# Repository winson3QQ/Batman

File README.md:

# Batman — Wi-Fi HaLow mesh on Raspberry Pi 4

Field notes from getting a **Morse Micro MM6108** Wi-Fi HaLow (802.11ah) radio working
over **SPI** on a Raspberry Pi 4, and building it into a batman-adv mesh node.

Hardware: Raspberry Pi 4 Model B + **Seeed WM1302 Pi HAT** + **Seeed Wio-WM6108**
mPCIe card (Quectel FGH100M-H / Morse Micro MM6108A1).

---

## TL;DR — the finding

The Morse Micro `morse_spi` driver fails to probe on a **stock** Raspberry Pi OS kernel:

```
morse_spi spi0.0: failed to init SPI with CMD63 (ret:-71)
```

The driver's SPI init sequence must send 144 training clocks with **chip-select
deasserted**. It does that by temporarily setting `SPI_CS_HIGH` to invert CS polarity.

On kernels **≥ 6.1** with **GPIO-descriptor chip-selects** (`cs-gpios`, which the
Pi 4 base device tree always uses), the SPI core sets `SPI_CS_HIGH` *itself* and
handles polarity through the GPIO descriptor flags. The driver's `|= SPI_CS_HIGH`
therefore becomes a **no-op**, and the training clocks go out with CS **asserted**.
The chip counts them as real bus traffic and its bit counter ends up exactly
**2 bits out of phase** for the rest of the session.

**Fix:** use `SPI_NO_CS` instead, so the core skips CS toggling entirely and the pin
stays high during training. → [`patches/0001-spi-use-SPI_NO_CS-for-training-sequence.patch`](patches/0001-spi-use-SPI_NO_CS-for-training-sequence.patch)

This is only needed because stock Raspberry Pi OS does **not** carry Morse Micro's
kernel patch (the one that defines `SPI_CONTROLLER_ENABLE_CS_GPIOD`). Their own
OpenWrt / `MorseMicro/rpi-linux` builds do.

Three things were required, all necessary:

1. Driver from the **MM6108 product line** — tag `mm6108-2.0.1`, *not* `mm8108-*`
2. The **`SPI_NO_CS` patch** above
3. Module parameters `enable_ext_xtal_init=1 bcf=bcf_fgh100mhaamd.bin`

Result:

```
morse_spi spi0.0: Loaded firmware from morse/mm6108.bin, size 468304, crc32 0xbe7b5c8f
morse_spi spi0.0: Loaded BCF from morse/bcf_fgh100mhaamd.bin, size 1251, crc32 0x941b2a82
```

---

## Then: the shortcut we should have found first

After all of the above, the driver worked — but a HaLow *link* still could not be
established, because Debian's stock `wpa_supplicant` (v2.10) contains **zero** S1G /
802.11ah support, and `hostapd` / `morse_cli` were not present at all.

It turns out **[OpenMANET](https://openmanet.github.io/docs/)** publishes a prebuilt
OpenWrt image for *exactly* this hardware combination — it lists
"Seeed WM1302 + Wio-WM6108" as a supported SPI setup, and the image ships
`wpa_supplicant_s1g`, `hostapd_s1g`, `morse-bcf-info` and `batctl` alongside the driver,
with 802.11s + BATMAN-V already wired up.

Its `mm610x-spi.dtbo` uses the **identical GPIO mapping** we had arrived at by hand.

**Lesson:** search for prebuilt firmware before rebuilding a vendor driver. The
`SPI_NO_CS` finding still stands for anyone running the Morse driver on a stock,
unpatched kernel — but if you just want a working mesh node, flash OpenMANET.

See [`docs/openmanet.md`](docs/openmanet.md).

---

## Contents

| Path | What |
|---|---|
| [`docs/hardware.md`](docs/hardware.md) | Hardware stack, GPIO map, device tree |
| [`docs/root-cause.md`](docs/root-cause.md) | Symptom → diagnosis → root cause, in full |
| [`docs/building-the-driver.md`](docs/building-the-driver.md) | Build instructions and the gotchas |
| [`docs/openmanet.md`](docs/openmanet.md) | The OpenMANET route |
| [`docs/flashing-and-recovery.md`](docs/flashing-and-recovery.md) | **Why `dd`-flashing an OpenWrt image leaves the old config intact**, and how to tell |
| [`docs/led-indicator.md`](docs/led-indicator.md) | Two-LED field status indicator — what each pattern means and why |
| [`docs/cloning-a-node.md`](docs/cloning-a-node.md) | **Building the second node by copying the first**, and the seven values that must not be copied |
| [`docs/pi5-rp1-bringup.md`](docs/pi5-rp1-bringup.md) | **Pi 5 / Pi 500 (RP1) only** — the two RP1-specific root causes and the Pi 5 overlays |
| [`patches/`](patches/) | The `SPI_NO_CS` patch |
| [`scripts/`](scripts/) | `flash-card.sh` (write + actually clear a card), `meshled` (LED daemon), `meshtest` (mesh health report), the uci cloning tools |
| [`tools/`](tools/) | Python SPI diagnostic scripts (via `spidev`) |

## Also worth reading

If you flash OpenWrt to SD cards with `dd`, [`docs/flashing-and-recovery.md`](docs/flashing-and-recovery.md)
is the most generally useful thing here. The image covers only the boot partition and
the squashfs — the `rootfs_data` overlay after it is never written, so the device boots
with its entire previous configuration restored while every verification you would
normally run comes back green.

## Status

- ✅ Driver probes, firmware + BCF load, netdev appears
- ✅ Root cause understood and patched
- ✅ OpenMANET 1.7.0 `rpi4-mm6108-spi` flashed, overlay wiped, **booted and verified**
- ✅ HaLow radio up under OpenMANET: `RPI RPI4-MM6108 (SPI)`, `wlan0`, 923 MHz @ 2 MHz BW, 27 dBm
- ✅ Node 1 configured: 802.11s mesh + SAE, BATMAN_V, hostname `manet01`, 2.4 GHz off
- ✅ Two-LED field status indicator installed and verified — [`docs/led-indicator.md`](docs/led-indicator.md)
- ✅ Node 2 built by **cloning node 1's uci config**, no wizard — [`docs/cloning-a-node.md`](docs/cloning-a-node.md)
- ✅ Second MM6108 set probes and loads firmware, radio up at 923 MHz / 2 MHz
- ⏳ Two nodes not yet powered simultaneously, so the mesh has not been formed
- ⏳ TX still not proven to radiate — the first `batctl n` neighbour will settle it
- ⏳ `meshtest` written but not yet run against a real peer

## License

Repository content is MIT (see [`LICENSE`](LICENSE)), except where noted:
- The patch in `patches/` applies to Morse Micro's driver, which is GPL-2.0-or-later;
  the patch is offered under the same terms as the code it modifies.
- `deploy/ots/patches/` contains a modified OpenTAKServer source file and its patch/generator,
  which are GPL-3.0-or-later like OpenTAKServer itself (see that directory's README).

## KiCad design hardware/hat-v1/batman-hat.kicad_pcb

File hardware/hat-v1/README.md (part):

# Batman HAT v1：電路圖（M2）

設計規格見 [`docs/design/hat-v1-spec.md`](../../docs/design/hat-v1-spec.md)。本資料夾是依規格產生的 **KiCad 7 電路圖**，狀態：**草稿，尚未送板廠**。

## 看圖

- **PDF**：[`out/batman-hat-schematic.pdf`](out/batman-hat-schematic.pdf)，共 10 頁：總覽 1 頁，加上 9 個功能區塊各 1 頁。
- **自動檢查報告**：[`out/check-report.md`](out/check-report.md)
- **材料清單草稿**：[`out/bom-draft.csv`](out/bom-draft.csv)。LCSC 料號在 M3 階段補齊。
- **用 KiCad 開**：開 `batman-hat.kicad_pro`。

### 這份電路圖怎麼讀

- 採用「**標籤式**」畫法：元件之間不拉長線，每支腳旁邊標一個**網路名稱**，**名稱相同就代表接在一起**。
  - 方框形的標籤是跨頁共用的網路。
  - 純文字的標籤只在該頁內使用。
- 腳上打 **×** 的，是刻意不接。
- 被紅色 **×** 劃掉的元件是**預留不焊**（DNP），用來日後微調。
- 每頁左下角的 **NOTES** 寫了每個元件為什麼這樣接、數值怎麼來的。

| 頁 | 檔案 | 內容 |
|---|---|---|
| 2 | `power_in` | 電池焊墊、突波保護、eFuse 與反接保護、整台電流量測（INA226 #1）、電池偵測 |
| 3 | `power_5v` | 5 V 降壓（給 Pi）、理想二極體（防止 Pi 的 USB-C 倒灌）、綠燈 |
| 4 | `power_3v3` | 電源二選一（電池 / Pi 5 V）、3.3 V 降壓（給 HaLow）、HaLow 電流量測（INA226 #2）、濾波 |
| 5 | `softpower` | LTC2955 軟開關機、AUTO-ON 跳線、電源鍵 |
| 6 | `pi_header` | 40-pin 排母、固定孔（2026-09-28 拿掉 ID EEPROM，改用 `config.txt`） |
| 7 | `halow` | mPCIe 插座（Wio-WM6108）、大電容 |
| 8 | `security` | TPM 2.0 SLB9672、ATECC608C、RTC RV-3028 與超級電容 |
| 9 | `gnss` | MAX-M10S 定位模組、主動式天線供電、U.FL |
| 10 | `debug` | Tag-Connect 除錯焊墊、所有測試點（值欄寫了正常讀值）、電源旗標 |

## 怎麼產生（不要直接改 `.kicad_sch`）

**唯一的資料來源是 `gen/design.py`**：所有元件、數值、接線都寫在這裡。改完後執行：

```sh
./build.sh      # 需要 KiCad 7（kicad-cli）與 python3
```

依序產生：

1. 電路圖
2. 檢查報告
3. 材料清單
4. PDF

檢查沒過就停下來，並印出錯誤。

| 檔案 | 作用 |
|---|---|
| `gen/design.py` | 設計資料：元件、數值、接線，以及檢查程式要用的規格事實（GPIO 表、電壓上限） |
| `gen/symbols.py` | 元件符號與接腳對照 |
| `gen/gen_sch.py` | 產生 KiCad 7 電路圖 |
| `gen/check.py` | 檢查（見下） |
| `gen/bom.py` | 材料清單草稿 |

## 自動檢查做了什麼

`gen/check.py` 會做以下檢查：

1. **接線比對**：請 KiCad 自己匯出接線表（netlist），和 `design.py` **逐腳比對**，目前 557 支腳全部一致。產生程式若有錯，例如標籤沒對到腳、兩個網路被接在一起，這一步會抓到。
2. **GPIO 表**：Pi 排針的 28 支 GPIO 和規格 §4.2 逐一比對。
3. **I2C 位址**不重複：0x36 / 0x40 / 0x41 / 0x52。
4. **TPM 與 SPI1 網路上沒有任何測試點**（規格 §5.1 的資安要求）。
5. **電壓上限**：
   - 對有耐壓限制的接腳（例如 TPS62933F 的 EN 最高 6 V、LTC2955 的 KILL 最高 6 V），用該網路最壞情況的電壓比對規格書的絕對最大值。
   - 接到 Pi GPIO 的網路都不可超過 3.3 V。
6. **只接到一支腳的網路**：這類網路列為錯誤，除非在 `SINGLE_PIN_OK` 寫明理由（例如只接測試點的除錯腳）。
7. **設定點**：從電阻值反算以下各項，和規格比對：
   - eFuse 的欠壓 / 過壓 / 限流門檻
   - 5 V 與 3.3 V 的輸出電壓
   - 5 V 降壓的硬體欠壓門檻
   - AUTO-ON 門檻

KiCad 7 的命令列沒有 ERC（電氣規則檢查），上面這些自寫檢查就是替代。用 KiCad 圖形介面開啟時，仍可手動執行 ERC 做第二道檢查。

## 已知待辦（送板廠前必須完成）

| 項目 | 狀態 |
|---|---|
| `batman:` 開頭的自製封裝 | ✅ mPCIe 5.2H、RV-3028 已依原廠圖面畫好；TI 功率 FET、SLB9672 改用 KiCad 內建封裝；**CPH3225A、電池焊墊、卡片固定柱仍是佔位封裝** |
| LCSC 料號、JLC 基礎料 / 擴展料、庫存 | M3 |
| 電感、磁珠的實際型號與規格（Isat、DCR） | M3 查證 |
| MAX-M10S 的 VIO_SEL、V_BCKP 接法 | ✅ 已依規格書 R08 確認：VIO_SEL 空接 = 3.3 V、V_BCKP 1.65–3.6 V 接 3.3 V |
| GNSS 主動式天線供電與短路偵測 | ✅ 依整合手冊 R05 圖 38 的**三腳天線監控**：P-FET 開關（LNA_EN 控制）、10 Ω 感測電阻、OPA333 比較器 → 偵測短路 / 斷線並自動切斷、恢復天線供電；天線由 3V3_GNSS 供電（不再受 VCC_RF 50 mA 限制）。GNSS 的 I2C 腳改作監控用（CFG-I2C-ENABLED=0） |
| RV-3028 的 EVI 閒置處理 | ✅ Application Manual §7.1：「EVI 不可空接，經電阻接 VSS」→ 維持 100 kΩ 到地；另依 §7.3 在 VBACKUP 加 100 nF（C77） |
| 卡片固定柱高度 | 第一批板子量測（規格 V14） |

## 對抗式審查修正紀錄（電路圖 v0.1，2026-09-27）

兩位獨立審查者。

- **電源審查**：沒有阻斷級問題，3 個重大、7 個次要。
- **數位 / 資安 / 製造審查**：1 個阻斷級、4 個重大、6 個次要。
- 兩份審查都確認：接腳、I2C 位址、GPIO 對應都沒有接錯。

以下是修正項目：

| 嚴重度 | 問題 | 修正 |
|---|---|---|
| 重大 | AUTO-ON 門檻（6.25 V）可能低於 5 V 降壓的開機門檻：電池慢慢回升時，LTC2955 先開、Pi 還沒電 → 0.5 秒後又關掉，而且之後不會再自動開機 | R31 改 787 kΩ → AUTO-ON 7.10 V（最低 6.74 V，高於降壓的最高門檻 6.55 V）；檢查程式加入最壞情況比對 |
| 重大 | BENCH 跳線焊上後，R23 拖低 LTC_ENB，LTC2955 關不掉 5 V → 電池供電時無法斷電 | R23 改 4.7 MΩ（2026-09-28 方案 D 後 BENCH 已取消，R23 改當 EN 上拉） |
| 重大 | 過壓切斷點（18.0–18.7 V）離 4S 滿電 16.8 V 太近；插電池的振鈴會觸發過壓，且可能一直關著不恢復 | R3 改 1.50 MΩ → 19.2 V 切斷、最低 17.44 V 恢復；電池輸入加 1 Ω + 10 µF 阻尼 |
| 重大 | A 級元件在 KiCad 沒標不焊，匯出給 JLC 會被一起焊上 | A 級元件自動標為 DNP（電路圖上會被劃掉，這是刻意的：由台灣補焊） |
| 重大 | 天線線短路 → 0402 電阻燒掉、拖垮 Pi 3.3 V | R81 改 47 Ω 1206（短路約 70 mA、0.23 W，在額定內）；待整合手冊再確認 |
| 重大 | 量產板的 Tag-Connect 仍接著 HaLow SPI（金鑰會經過）與 root 序列埠 | 每條線串 0 Ω（R40–R47）：開發板焊、量產板不焊；VCC 腳串 1 kΩ（R48） |
| 重大 | 材料清單無法直接下單 | 只有銅箔的項目（測試焊墊、跳線、固定孔、Tag-Connect）移出材料清單；LCSC 料號在 M3 補齊 |
| 阻斷 | 自製封裝不存在 | 可用現成的先換：電感 `L_Coilcraft_XxL4030`、TI 功率電晶體 `VSON-8 NexFET`（汲極合併為第 5 腳）、TPM `QFN-32 5×5 散熱墊 3.6 mm`。其餘（mPCIe、RTC、超級電容、電池焊墊、固定柱）在 M4 建立 |
| 次要 | 電容耐壓與直流偏壓降容；eFuse IN 腳缺電容；TPS62933F EN 只有 0.7 µA 上拉、容易受干擾；5 V 最壞可到 5.33 V | 輸入電容改 10 µF 50 V X7R 1210；VCAP 改 220 nF 25 V；加 C9 100 nF、C32 2.2 nF；R13/R14 改 0.5%（最壞 5.29 V） |
| 次要 | 待機耗電約 2 mA（主要是 eFuse 本身） | 電池偵測分壓改 1 MΩ；其餘寫進文件（3 Ah 約 60 天放完） |
| 次要 | GPIO14/15 在 Pi 4 預設是 mini-UART，不是 UART0 | 網路改名 `CONSOLE_TX/RX` |
| 次要 | LED 規格要 0402 | 改 0402 |
| 次要 | 隔離跳線切斷後，晶片仍會經 I2C / SPI / UART 被反向供電 | 寫進元件備註 |
| 次要 | I2C 400 kHz 時 ATECC608 喚醒脈衝不夠長 | 軟體維持 100 kHz（寫進規格 §7） |
| 次要 | 沒有光學定位點 | M4 畫電路板時加 3 個 |

**已知、接受的行為**（寫給使用者）：
- 用 USB-C 開發時才插上電池（且沒焊 AUTO-ON），LTC2955 會以「關機」狀態啟動，把 HaLow 的 3.3 V 關掉 → 先插電池再插 USB-C，或按一下電源鍵。
- LTC2955 開機遮蔽期間（最多 0.72 秒），HaLow 卡可能經 SPI 腳微量反向供電給 Pi。

## 第一版擺位（M4 第 1 步，尚未走線）

- **產生方式**：`python3 gen/gen_fp.py && python3 gen/gen_pcb.py`，會產生 `batman-hat.kicad_pcb`、[`out/floorplan.png`](out/floorplan.png) 與 [`out/floorplan-report.md`](out/floorplan-report.md)。
- **固定位置的零件**依機構尺寸擺放：
  - HAT 外框 65 × 56.5 mm
  - 40-pin 排母（在背面）
  - 4 個固定孔
  - mPCIe 插座與卡片外框：卡片平躺在板子上方，插座在右側
- **其他零件**依功能分區自動排，**卡片正下方只放 ≤ 1.9 mm 高**、不發熱、不需要摸得到的零件。
- **自製封裝**：`batman.pretty` 裡的 mPCIe 插座是照連欣規格書畫的；RTC 依 Application Manual §8.1 畫好；超級電容、電池焊墊、固定柱是**佔位封裝**（標 PLACEHOLDER），送板廠前要依原廠焊墊圖重畫。
- **Pi 4 Wi-Fi 天線禁佈區**的位置是推論，要對照 Pi 4 機構圖確認。

### 測試點（使用者決定，2026-09-27）

| 類型 | 位置 | 內容 |
|---|---|---|
| 可夾的大焊墊（Keystone 5015） | 正面 | 電池 VBAT、5V、HaLow 3.3V、GND |
| 小探針焊墊（1–1.5 mm） | **背面（接 Pi 那面）** | 其他電源軌、eFuse / 降壓 / 軟開關機的控制訊號、GNSS 重置、RTC 輸出、分流電阻的 Kelvin 點 |
| 不另設測試點 | 40-pin 排母的焊點（穿到正面露出） | I2C、UART5、PPS、INT/KILL、BAT_PRESENT、ALERT、HaLow reset/wake（清單在 `design.py` 的 `HEADER_PROBE`，檢查程式會確認都在排針上） |

- **怎麼量背面的焊墊**：焊墊都排在板子左、右、下三邊、離板邊約 3 mm 內。用 40-pin 延長排針（stacking header）把 HAT 墊高，探針就能從側面點到；要長時間觀察（示波器看時序）就焊一條 30 AWG 細線拉出來。
  - 左邊：eFuse / 軟開關機 / 5 V 控制訊號
  - 右邊：GNSS / RTC 相關
  - 下邊：其他電源軌
- **TPM / SPI1 仍然不設任何測試點。**

### 雜訊擺位原則（2026-09-27）

- **兩顆降壓的開關核心放在板子下緣**，也就是晶片、電感、輸入電容這幾顆：
  - 遠離右上角的 GNSS，距離約 35 mm。
  - 遠離左邊 HaLow 卡的天線端。
- **這兩組的直流側零件放在卡片下方、最靠近下緣的一條**：輸出電容、理想二極體。
- **上方長條只放安靜的零件**：GNSS、Tag-Connect、可夾測試點、eFuse。eFuse 不會切換開關，所以不產生開關雜訊。
- **實際效果仍需上機量測**，見規格 V7 / V11：降壓滿載時 GNSS 的 C/N0（載波雜訊比，衡量衛星訊號強度），以及 HaLow 接收靈敏度。

## 送板廠前的模擬（`python3 sim/run_all.py` → [`out/sim/sim-report.md`](out/sim/sim-report.md)）

| 項目 | 工具 | 結果 |
|---|---|---|
| S1 插電池瞬間的振盪 | ngspice（KiCad 內建） | 原本 1 Ω + 10 µF 阻尼在 16.8 V 時會衝到 20.1 V → 改成 **0.47 Ω + 2 × 10 µF**。線長 ≤ 0.7 m 時峰值低於過壓門檻。1.5 m 長線仍會略超過，但持續 7.8 µs，短於 eFuse 最短反應時間 8.5 µs；就算觸發也只是延後開機，不會損壞 |
| S2 HaLow 3.3 V：π 濾波 + 發射突波 | ngspice | 1.2 A 突波下插座端最低 3.26 V（mPCIe 下限 3.0 V）；濾波共振 78 mΩ @ 13.8 kHz。**聚合物電容 C62 必要**：拿掉的話共振升到 250 mΩ |
| S3 開關機情境（8 種） | 依規格書寫的行為模型 | 全部符合設計意圖 |
| S4 電池慢慢回升（蒙地卡羅，400 次） | 行為模型 | 目前設計 **0 / 400** 卡在關機；審查前的 681 kΩ 有 274 / 400 卡住 → 證實審查的修正是必要的 |

- 所有假設（線長、電容降額、HaLow 發射電流等）都列在報告最後一節，有更準的數據時改數字重跑即可。
- 雜訊干擾 GNSS / HaLow 無法可靠模擬，仍需第一批板子實測（規格 V7 / V11）。

## LCSC 料號（M3 草稿，`gen/lcsc.py` → [`out/lcsc-report.md`](out/lcsc-report.md)、[`out/bom-jlc.csv`](out/bom-jlc.csv)）

這個環境連不到 JLC 和 LCSC 官網（網路政策擋住），所以用以下三個離線來源：

1. **jlcparts 完整資料庫**：GitHub 公開，2026-09-27 16:21 UTC 快照，101 萬筆。
   - 限制：目前只收 LCSC 編號 **C6374508 以後**的零件，所以舊編號的零件查不到，包括大部分基礎料和 TI 的 IC。
2. **JLC 基礎料 / 優選料編號清單**：CDFER/jlcpcb-parts-database 每日自動抓取，2026-09-27 更新，共 3,493 個編號。只有編號，沒有規格。
3. **常用基礎料對照**：例如 0402 10 kΩ = C25744。這是記憶中的對照，只有在該編號**確認列於基礎料清單**時才採用；「編號對應什麼規格」要在上傳 JLC 時核對。

| 狀態 | 行數 | 意思 | 你要做的 |
|---|---|---|---|
| DB | 23 | 快照裡查到，有庫存 | 下單前看一下庫存有沒有變 |
| BASIC-verify | 13 | JLC 基礎料（省擴展料費） | 上傳 BOM 後，核對 JLC 顯示的規格和報告「note」欄一致 |
| SEARCH | 32 | 快照裡沒有 | 到 jlcpcb.com/parts 用 MPN 搜尋，或讓 JLC 的 BOM 工具依 MPN 自動配對 |
| NOT-JLC | 40 | A 級元件（台灣補焊）或只有銅箔 | A 級向 DigiKey / Mouser 等原廠授權通路採購 |
| DNP | 2 | 不焊 | — |

- **中國廠商**：SURGING（SMBJ20CA）、hongjiacheng（BSS138）、FOJAN（3.9 kΩ）、Chinocera（47 µF）、連欣（mPCIe 插座），都是 C 級被動 / 分離元件，依規格 §5.8 可用。報告的「origin」欄標了每一家的總部所在地。
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
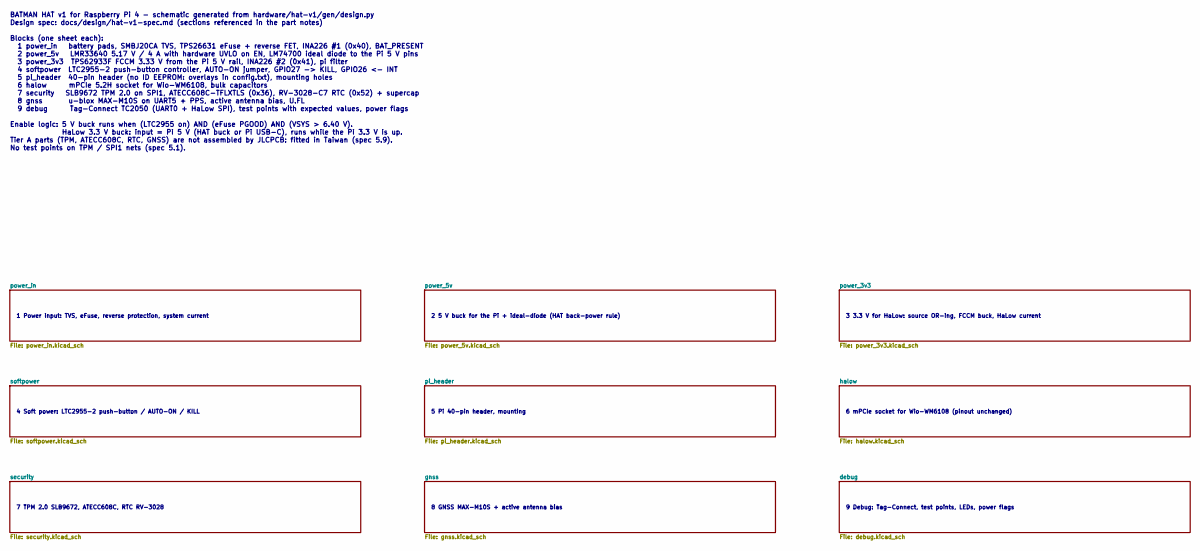
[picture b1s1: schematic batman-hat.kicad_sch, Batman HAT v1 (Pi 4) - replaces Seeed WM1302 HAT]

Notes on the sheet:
1 Power input: TVS, eFuse, reverse protection, system current
2 5 V buck for the Pi + ideal-diode (HAT back-power rule)
3 3.3 V for HaLow: source OR-ing, FCCM buck, HaLow current
4 Soft power: LTC2955-2 push-button / AUTO-ON / KILL
5 Pi 40-pin header, mounting
6 mPCIe socket for Wio-WM6108 (pinout unchanged)
7 TPM 2.0 SLB9672, ATECC608C, RTC RV-3028
8 GNSS MAX-M10S + active antenna bias
9 Debug: Tag-Connect, test points, LEDs, power flags
BATMAN HAT v1 for Raspberry Pi 4 - schematic generated from hardware/hat-v1/gen/design.py Design spec: docs/design/hat-v1-spec.md (sections referenced in the part notes) Blocks (one sheet each): 1 power_in battery pads, SMBJ20CA TVS, TPS26631 eFuse + reverse FET, INA226 #1 (0x40), BAT_PRESENT 2 pow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

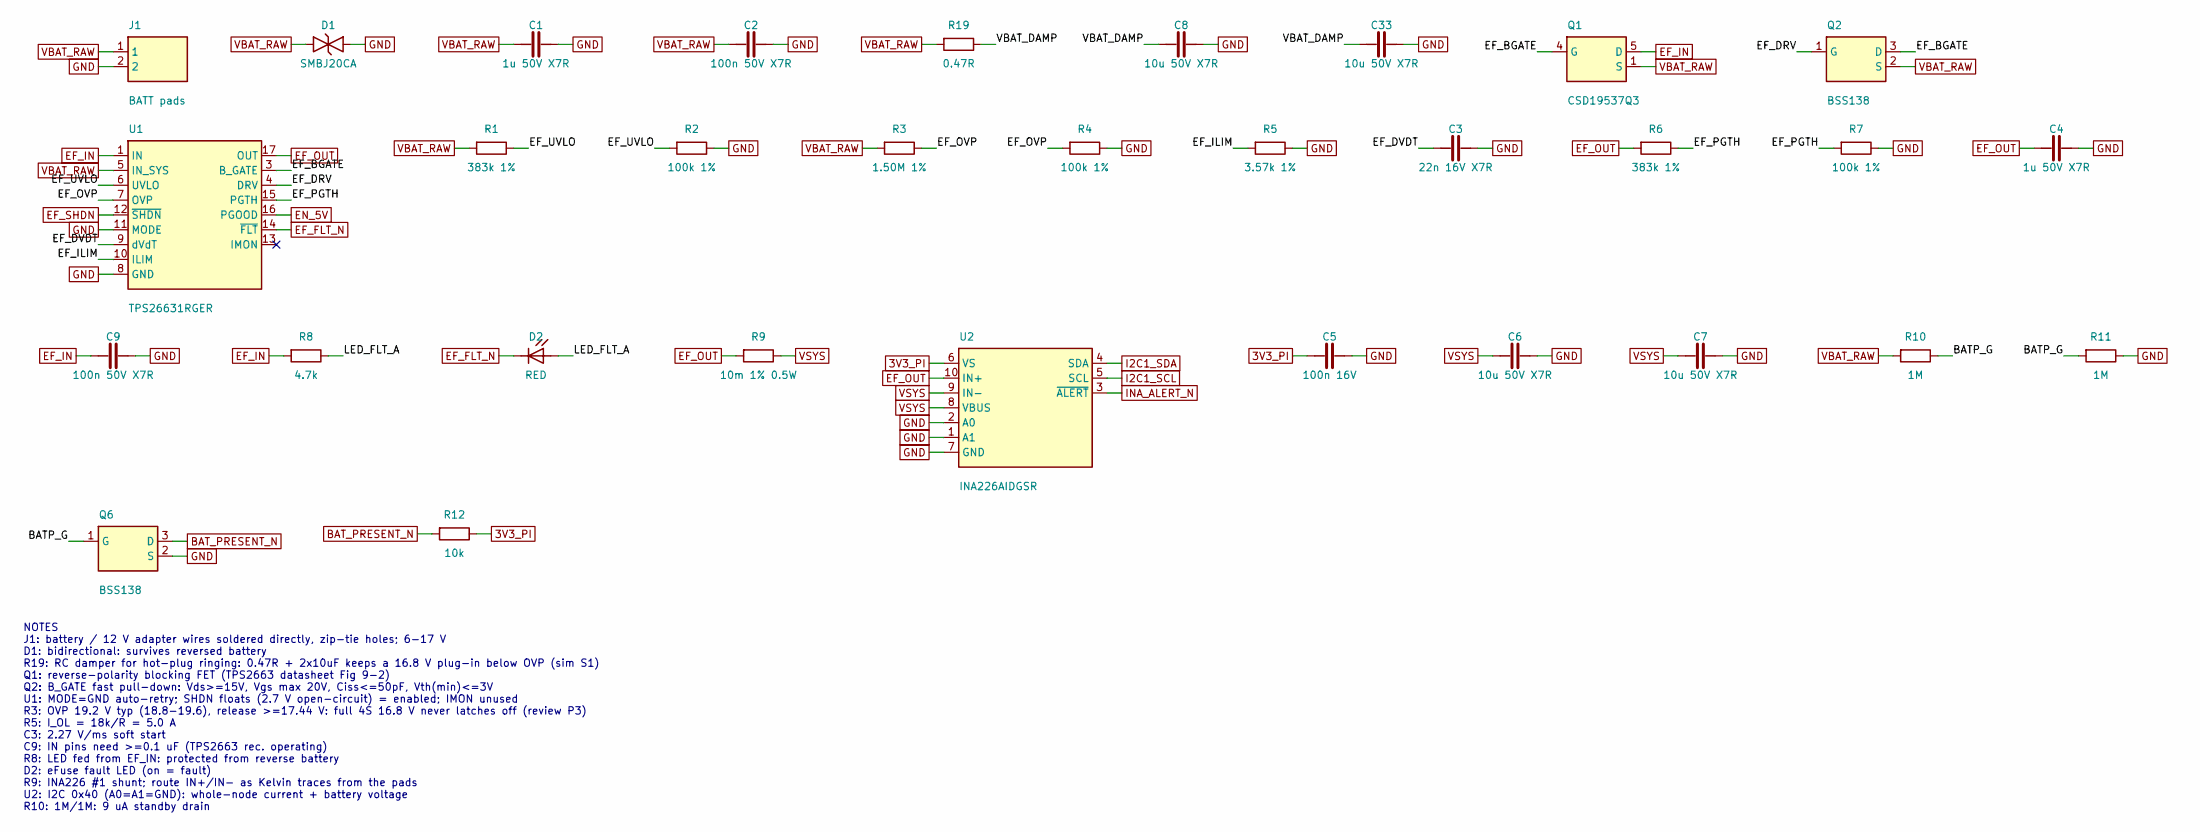
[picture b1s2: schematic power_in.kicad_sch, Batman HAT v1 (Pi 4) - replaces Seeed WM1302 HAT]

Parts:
C1, C4: 1u 50V X7R; C_0805_2012Metric
C2, C9: 100n 50V X7R; C_0402_1005Metric
C3: 22n 16V X7R; C_0402_1005Metric
C5: 100n 16V; C_0402_1005Metric
C6, C7, C8, C33: 10u 50V X7R; C_1210_3225Metric
D1: SMBJ20CA; D_SMB; MPN SMBJ20CA
D2: RED; LED_0402_1005Metric
J1: BATT pads; BattPads_2x_3x5mm_StrainRelief
Q1: CSD19537Q3; VSON-8_3.3x3.3mm_P0.65mm_NexFET; MPN CSD19537Q3
Q2, Q6: BSS138; SOT-23; MPN BSS138
R1, R6: 383k 1%; R_0402_1005Metric
R2, R4, R7: 100k 1%; R_0402_1005Metric
R3: 1.50M 1%; R_0402_1005Metric
R5: 3.57k 1%; R_0402_1005Metric
R8: 4.7k; R_0603_1608Metric
R9: 10m 1% 0.5W; R_1206_3216Metric
R10, R11: 1M; R_0402_1005Metric
R12: 10k; R_0402_1005Metric
R19: 0.47R; R_0805_2012Metric
U1: TPS26631RGER; Texas_RGE0024H_VQFN-24-1EP_4x4mm_P0.5mm_EP2.7x2.7mm_Thermal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; MPN TPS26631RGER
U2: INA226AIDGSR; VSSOP-10_3x3mm_P0.5mm; MPN INA226AIDGSR

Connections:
BATP_G: Q6.1 (G), R10.2, R11.1
BAT_PRESENT_N: Q6.3 (D), R12.1; also elsewhere on the board
EF_BGATE: Q1.4 (G), Q2.3 (D), U1.3 (B_GATE)
EF_DRV: Q2.1 (G), U1.4 (DRV)
EF_DVDT: C3.1, U1.9 (dVdT)
EF_FLT_N: D2.1, U1.14 (~FLT); also elsewhere on the board
EF_ILIM: R5.1, U1.10 (ILIM)
EF_IN: C9.1, Q1.5 (D), R8.1, U1.1 (IN), U1.2 (IN)
EF_OUT: C4.1, R6.1, R9.1, U1.17 (OUT), U1.18 (OUT), U2.10 (IN+); also elsewhere on the board
EF_OVP: R3.2, R4.1, U1.7 (OVP)
EF_PGTH: R6.2, R7.1, U1.15 (PGTH)
EF_SHDN: U1.12 (~SHDN); also elsewhere on the board
EF_UVLO: R1.2, R2.1, U1.6 (UVLO)
EN_5V: U1.16 (PGOOD); also elsewhere on the board
GND: C1.2, C2.2, C3.2, C4.2, C5.2, C6.2, C7.2, C8.2, C9.2, C33.2, D1.2, J1.2, Q6.2 (S), R2.2, R4.2, R5.2, R7.2, R11.2, U1.8 (GND), U1.11 (MODE), U1.25 (GND), U2.1 (A1), U2.2 (A0), U2.7 (GND); also elsewhere on the board
I2C1_SCL: U2.5 (SCL); also elsewhere on the board
I2C1_SDA: U2.4 (SDA); also elsewhere on the board
INA_ALERT_N: U2.3 (~ALERT); also elsewhere on the board
LED_FLT_A: D2.2, R8.2
VBAT_DAMP: C8.1, C33.1, R19.2
VBAT_RAW: C1.1, C2.1, D1.1, J1.1, Q1.1 (S), Q1.2 (S), Q1.3 (S), Q2.2 (S), R1.1, R3.1, R10.1, R19.1, U1.5 (IN_SYS); also elsewhere on the board
VSYS: C6.1, C7.1, R9.2, U2.8 (VBUS), U2.9 (IN-); also elsewhere on the board

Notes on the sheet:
NOTES J1: battery / 12 V adapter wires soldered directly, zip-tie holes; 6-17 V D1: bidirectional: survives reversed battery R19: RC damper for hot-plug ringing: 0.47R + 2x10uF keeps a 16.8 V plug-in below OVP (sim S1) Q1: reverse-polarity blocking FET (TPS2663 datasheet Fig 9-2) Q2: B_GATE fast pu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

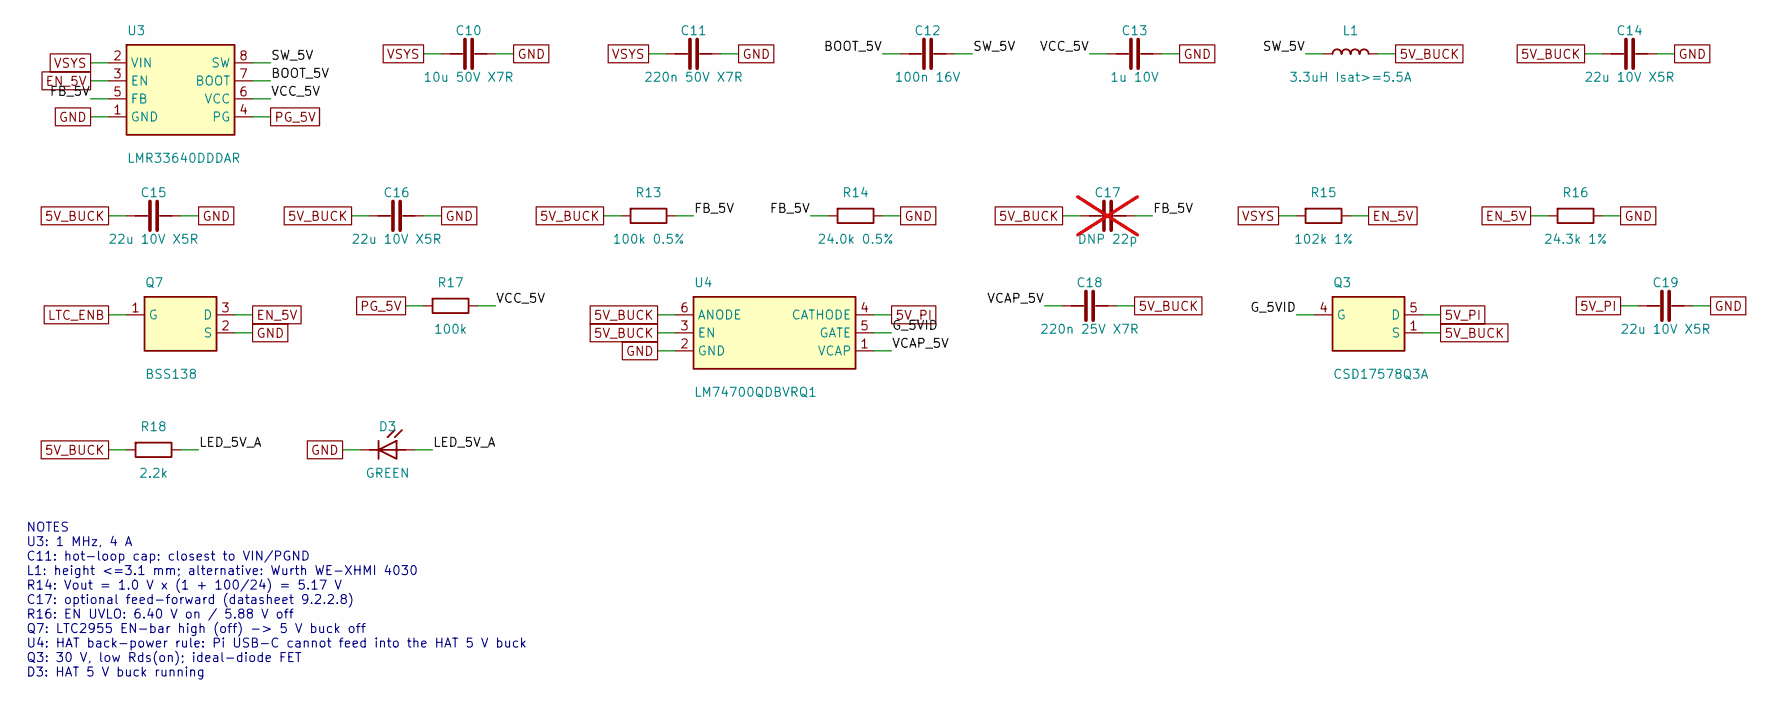
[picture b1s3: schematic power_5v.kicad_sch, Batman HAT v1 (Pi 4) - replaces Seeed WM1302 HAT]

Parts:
C10: 10u 50V X7R; C_1210_3225Metric
C11: 220n 50V X7R; C_0603_1608Metric
C12: 100n 16V; C_0402_1005Metric
C13: 1u 10V; C_0402_1005Metric
C14, C15, C16, C19: 22u 10V X5R; C_0805_2012Metric
C17: DNP 22p; C_0402_1005Metric; not fitted
C18: 220n 25V X7R; C_0603_1608Metric
D3: GREEN; LED_0402_1005Metric
L1: 3.3uH Isat>=5.5A; L_Coilcraft_XxL4030; MPN XGL4030-332MEC
Q3: CSD17578Q3A; VSON-8_3.3x3.3mm_P0.65mm_NexFET; MPN CSD17578Q3A
Q7: BSS138; SOT-23; MPN BSS138
R13: 100k 0.5%; R_0402_1005Metric
R14: 24.0k 0.5%; R_0402_1005Metric
R15: 102k 1%; R_0402_1005Metric
R16: 24.3k 1%; R_0402_1005Metric
R17: 100k; R_0402_1005Metric
R18: 2.2k; R_0402_1005Metric
U3: LMR33640DDDAR; Texas_HSOP-8-1EP_3.9x4.9mm_P1.27mm_ThermalVias; MPN LMR33640DDDAR
U4: LM74700QDBVRQ1; SOT-23-6; MPN LM74700QDBVRQ1

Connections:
5V_BUCK: C14.1, C15.1, C16.1, C17.1, C18.2, L1.2, Q3.1 (S), Q3.2 (S), Q3.3 (S), R13.1, R18.1, U4.3 (EN), U4.6 (ANODE); also elsewhere on the board
BOOT_5V: C12.1, U3.7 (BOOT)
EN_5V: Q7.3 (D), R15.2, R16.1, U3.3 (EN); also elsewhere on the board
FB_5V: C17.2, R13.2, R14.1, U3.5 (FB)
GND: C10.2, C11.2, C13.2, C14.2, C15.2, C16.2, C19.2, D3.1, Q7.2 (S), R14.2, R16.2, U3.1 (GND), U3.9 (GND), U4.2 (GND); also elsewhere on the board
G_5VID: Q3.4 (G), U4.5 (GATE)
LED_5V_A: D3.2, R18.2
LTC_ENB: Q7.1 (G); also elsewhere on the board
PG_5V: R17.1, U3.4 (PG); also elsewhere on the board
SW_5V: C12.2, L1.1, U3.8 (SW)
VCAP_5V: C18.1, U4.1 (VCAP)
VCC_5V: C13.1, R17.2, U3.6 (VCC)
VSYS: C10.1, C11.1, R15.1, U3.2 (VIN); also elsewhere on the board

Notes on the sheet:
NOTES U3: 1 MHz, 4 A C11: hot-loop cap: closest to VIN/PGND L1: height <=3.1 mm; alternative: Wurth WE-XHMI 4030 R14: Vout = 1.0 V x (1 + 100/24) = 5.17 V C17: optional feed-forward (datasheet 9.2.2.8) R16: EN UVLO: 6.40 V on / 5.88 V off Q7: LTC2955 EN-bar high (off) -> 5 V buck off U4: HAT back-p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

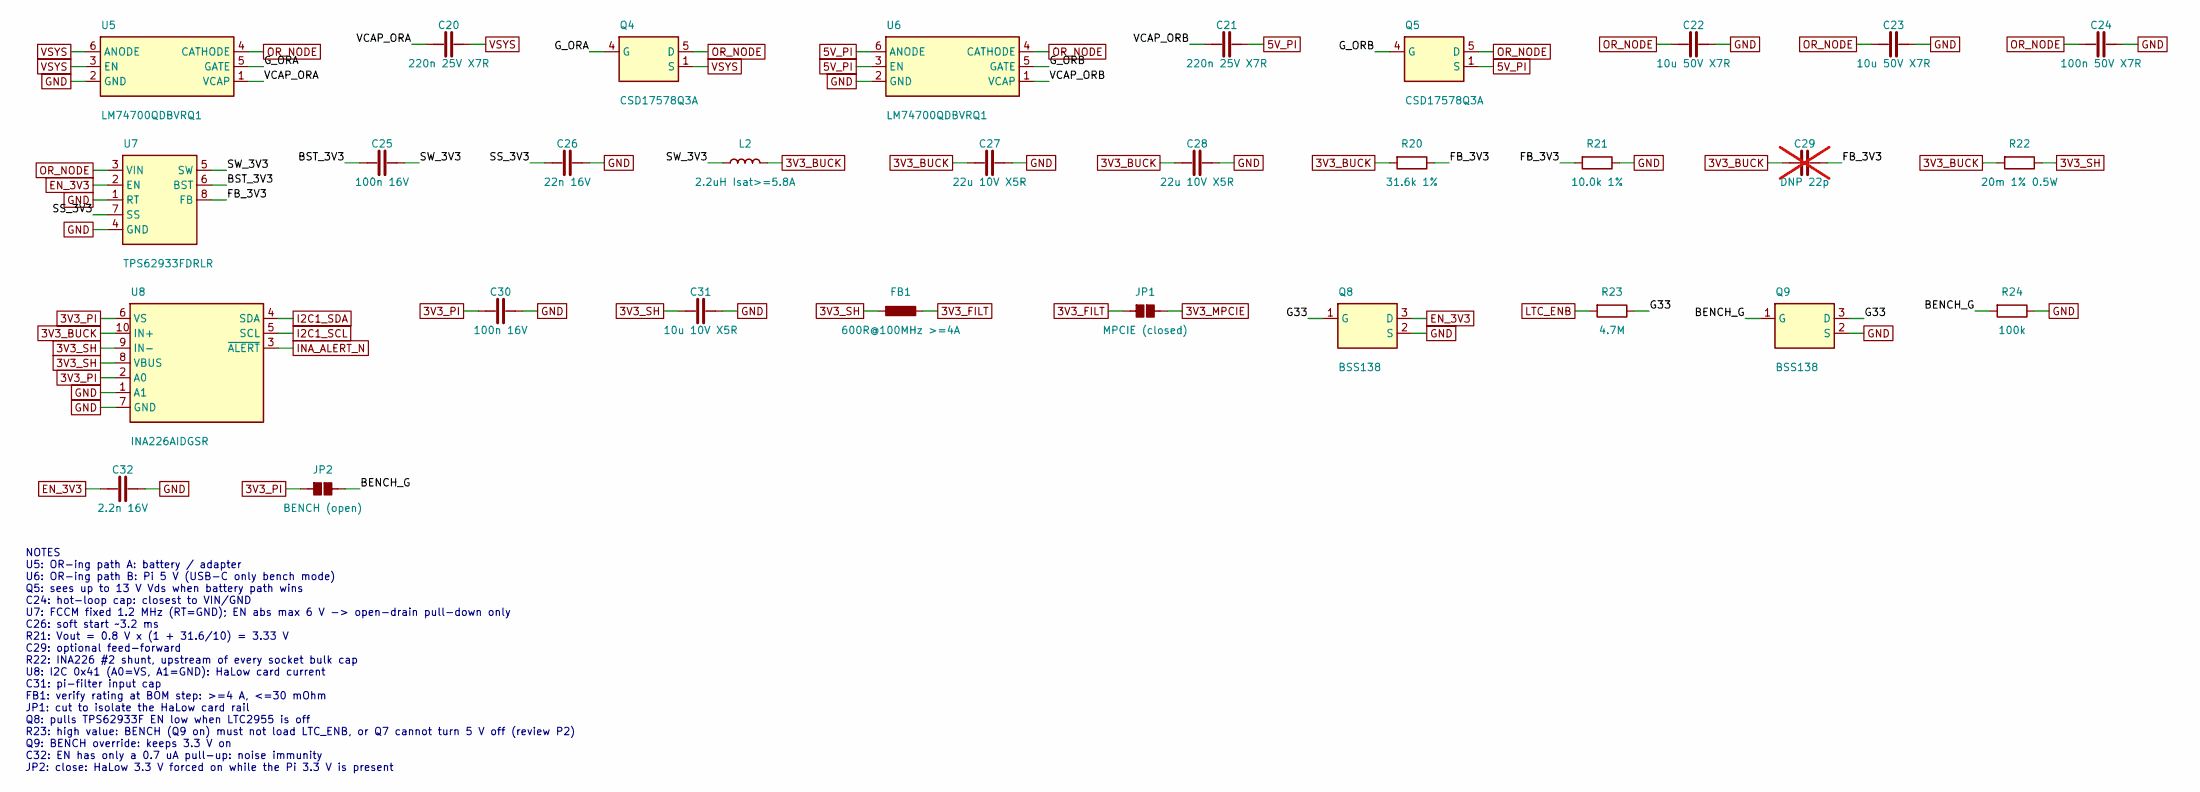
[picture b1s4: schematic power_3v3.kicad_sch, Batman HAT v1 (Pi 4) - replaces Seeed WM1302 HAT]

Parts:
C20, C21: 220n 25V X7R; C_0603_1608Metric
C22, C23: 10u 50V X7R; C_1210_3225Metric
C24: 100n 50V X7R; C_0402_1005Metric
C25, C30: 100n 16V; C_0402_1005Metric
C26: 22n 16V; C_0402_1005Metric
C27, C28: 22u 10V X5R; C_0805_2012Metric
C29: DNP 22p; C_0402_1005Metric; not fitted
C31: 10u 10V X5R; C_0603_1608Metric
C32: 2.2n 16V; C_0402_1005Metric
FB1: 600R@100MHz >=4A; L_1206_3216Metric; MPN BLM31KN601SN1L
JP1: MPCIE (closed); SolderJumper-2_P1.3mm_Bridged_RoundedPad1.0x1.5mm
JP2: BENCH (open); SolderJumper-2_P1.3mm_Open_RoundedPad1.0x1.5mm
L2: 2.2uH Isat>=5.8A; L_Coilcraft_XxL4030; MPN XGL4030-222MEC
Q4, Q5: CSD17578Q3A; VSON-8_3.3x3.3mm_P0.65mm_NexFET; MPN CSD17578Q3A
Q8, Q9: BSS138; SOT-23; MPN BSS138
R20: 31.6k 1%; R_0402_1005Metric
R21: 10.0k 1%; R_0402_1005Metric
R22: 20m 1% 0.5W; R_1206_3216Metric
R23: 4.7M; R_0402_1005Metric
R24: 100k; R_0402_1005Metric
U5, U6: LM74700QDBVRQ1; SOT-23-6; MPN LM74700QDBVRQ1
U7: TPS62933FDRLR; SOT-583-8; MPN TPS62933FDRLR
U8: INA226AIDGSR; VSSOP-10_3x3mm_P0.5mm; MPN INA226AIDGSR

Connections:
3V3_BUCK: C27.1, C28.1, C29.1, L2.2, R20.1, R22.1, U8.10 (IN+); also elsewhere on the board
3V3_FILT: FB1.2, JP1.1
3V3_MPCIE: JP1.2; also elsewhere on the board
3V3_SH: C31.1, FB1.1, R22.2, U8.8 (VBUS), U8.9 (IN-); also elsewhere on the board
BST_3V3: C25.1, U7.6 (BST)
FB_3V3: C29.2, R20.2, R21.1, U7.8 (FB)
GND: C22.2, C23.2, C24.2, C26.2, C27.2, C28.2, C30.2, C31.2, C32.2, Q8.2 (S), Q9.2 (S), R21.2, R24.2, U5.2 (GND), U6.2 (GND), U7.1 (RT), U7.4 (GND), U8.1 (A1), U8.7 (GND); also elsewhere on the board
I2C1_SCL: U8.5 (SCL); also elsewhere on the board
I2C1_SDA: U8.4 (SDA); also elsewhere on the board
INA_ALERT_N: U8.3 (~ALERT); also elsewhere on the board
unnamed: C20.1, U5.1 (VCAP)
unnamed: C20.2, Q4.1 (S), Q4.2 (S), Q4.3 (S), U5.3 (EN), U5.6 (ANODE)
unnamed: C21.1, U6.1 (VCAP)
unnamed: C21.2, Q5.1 (S), Q5.2 (S), Q5.3 (S), U6.3 (EN), U6.6 (ANODE)
unnamed: JP2.2, Q9.1 (G), R24.1
unnamed: Q4.4 (G), U5.5 (GATE)
unnamed: Q5.4 (G), U6.5 (GATE)
SS_3V3: C26.1, U7.7 (SS)
SW_3V3: C25.2, L2.1, U7.5 (SW)

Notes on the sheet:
NOTES U5: OR-ing path A: battery / adapter U6: OR-ing path B: Pi 5 V (USB-C only bench mode) Q5: sees up to 13 V Vds when battery path wins C24: hot-loop cap: closest to VIN/GND U7: FCCM fixed 1.2 MHz (RT=GND); EN abs max 6 V -> open-drain pull-down only C26: soft start ~3.2 ms R21: Vout = 0.8 V x 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

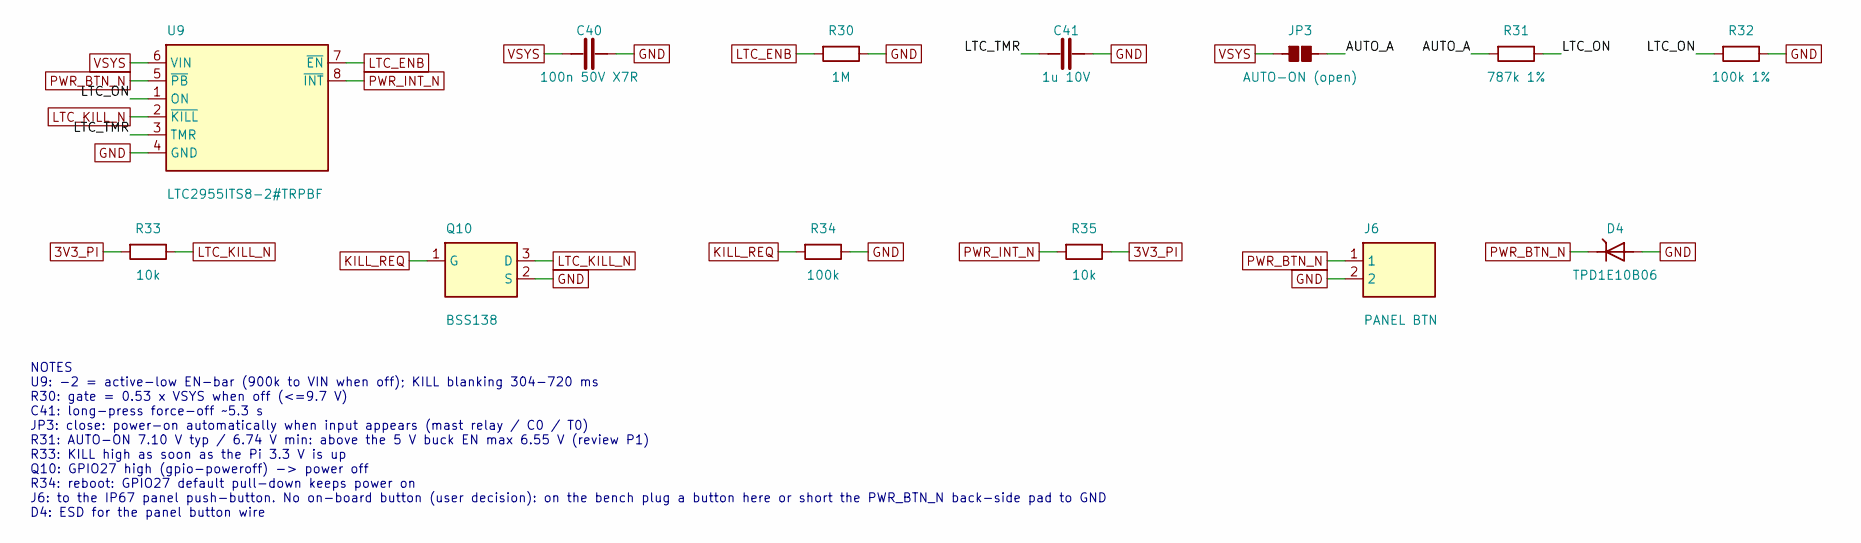
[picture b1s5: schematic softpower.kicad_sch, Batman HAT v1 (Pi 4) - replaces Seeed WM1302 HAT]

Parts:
C40: 100n 50V X7R; C_0402_1005Metric
C41: 1u 10V; C_0402_1005Metric
D4: TPD1E10B06; D_0402_1005Metric; MPN TPD1E10B06DPYR
J6: PANEL BTN; JST_SH_SM02B-SRSS-TB_1x02-1MP_P1.00mm_Horizontal; MPN SM02B-SRSS-TB
JP3: AUTO-ON (open); SolderJumper-2_P1.3mm_Open_RoundedPad1.0x1.5mm
Q10: BSS138; SOT-23; MPN BSS138
R30: 1M; R_0402_1005Metric
R31: 787k 1%; R_0402_1005Metric
R32: 100k 1%; R_0402_1005Metric
R33, R35: 10k; R_0402_1005Metric
R34: 100k; R_0402_1005Metric
U9: LTC2955ITS8-2#TRPBF; TSOT-23-8; MPN LTC2955ITS8-2#TRPBF

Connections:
AUTO_A: JP3.2, R31.1
GND: C40.2, C41.2, D4.2, J6.2, Q10.2 (S), R30.2, R32.2, R34.2, U9.4 (GND); also elsewhere on the board
KILL_REQ: Q10.1 (G), R34.1; also elsewhere on the board
LTC_ENB: R30.1, U9.7 (~EN); also elsewhere on the board
LTC_KILL_N: Q10.3 (D), R33.2, U9.2 (~KILL); also elsewhere on the board
LTC_ON: R31.2, R32.1, U9.1 (ON)
LTC_TMR: C41.1, U9.3 (TMR)
PWR_BTN_N: D4.1, J6.1, U9.5 (~PB); also elsewhere on the board
PWR_INT_N: R35.1, U9.8 (~INT); also elsewhere on the board
VSYS: C40.1, JP3.1, U9.6 (VIN); also elsewhere on the board

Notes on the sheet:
NOTES U9: -2 = active-low EN-bar (900k to VIN when off); KILL blanking 304-720 ms R30: gate = 0.53 x VSYS when off (<=9.7 V) C41: long-press force-off ~5.3 s JP3: close: power-on automatically when input appears (mast relay / C0 / T0) R31: AUTO-ON 7.10 V typ / 6.74 V min: above the 5 V buck EN max 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

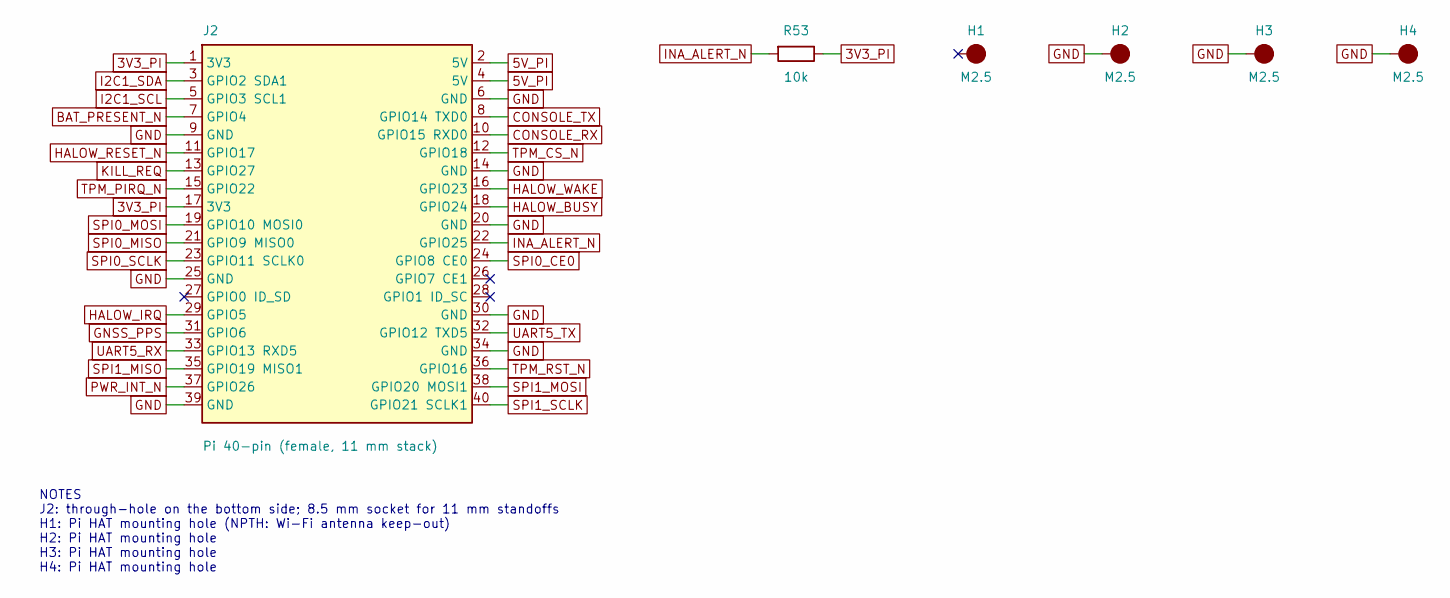
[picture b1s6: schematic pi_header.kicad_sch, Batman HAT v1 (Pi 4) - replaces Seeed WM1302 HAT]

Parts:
H1: M2.5; MountingHole_2.7mm_M2.5
H2, H3, H4: M2.5; MountingHole_2.7mm_M2.5_Pad_Via
J2: Pi 40-pin (female, 11 mm stack); PinSocket_2x20_P2.54mm_Vertical
R53: 10k; R_0402_1005Metric

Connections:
BAT_PRESENT_N: J2.7 (GPIO4); also elsewhere on the board
CONSOLE_RX: J2.10 (GPIO15 RXD0); also elsewhere on the board
CONSOLE_TX: J2.8 (GPIO14 TXD0); also elsewhere on the board
GND: H2.1, H3.1, H4.1, J2.6 (GND), J2.9 (GND), J2.14 (GND), J2.20 (GND), J2.25 (GND), J2.30 (GND), J2.34 (GND), J2.39 (GND); also elsewhere on the board
GNSS_PPS: J2.31 (GPIO6); also elsewhere on the board
HALOW_BUSY: J2.18 (GPIO24); also elsewhere on the board
HALOW_IRQ: J2.29 (GPIO5); also elsewhere on the board
HALOW_RESET_N: J2.11 (GPIO17); also elsewhere on the board
HALOW_WAKE: J2.16 (GPIO23); also elsewhere on the board
I2C1_SCL: J2.5 (GPIO3 SCL1); also elsewhere on the board
I2C1_SDA: J2.3 (GPIO2 SDA1); also elsewhere on the board
INA_ALERT_N: J2.22 (GPIO25), R53.1; also elsewhere on the board
KILL_REQ: J2.13 (GPIO27); also elsewhere on the board
PWR_INT_N: J2.37 (GPIO26); also elsewhere on the board
SPI0_CE0: J2.24 (GPIO8 CE0); also elsewhere on the board
SPI0_MISO: J2.21 (GPIO9 MISO0); also elsewhere on the board
SPI0_MOSI: J2.19 (GPIO10 MOSI0); also elsewhere on the board
SPI0_SCLK: J2.23 (GPIO11 SCLK0); also elsewhere on the board
SPI1_MISO: J2.35 (GPIO19 MISO1); also elsewhere on the board
SPI1_MOSI: J2.38 (GPIO20 MOSI1); also elsewhere on the board
SPI1_SCLK: J2.40 (GPIO21 SCLK1); also elsewhere on the board
TPM_CS_N: J2.12 (GPIO18); also elsewhere on the board
TPM_PIRQ_N: J2.15 (GPIO22); also elsewhere on the board
TPM_RST_N: J2.36 (GPIO16); also elsewhere on the board
UART5_RX: J2.33 (GPIO13 RXD5); also elsewhere on the board
UART5_TX: J2.32 (GPIO12 TXD5); also elsewhere on the board

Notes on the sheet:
NOTES J2: through-hole on the bottom side; 8.5 mm socket for 11 mm standoffs H1: Pi HAT mounting hole (NPTH: Wi-Fi antenna keep-out) H2: Pi HAT mounting hole H3: Pi HAT mounting hole H4: Pi HAT mounting hole

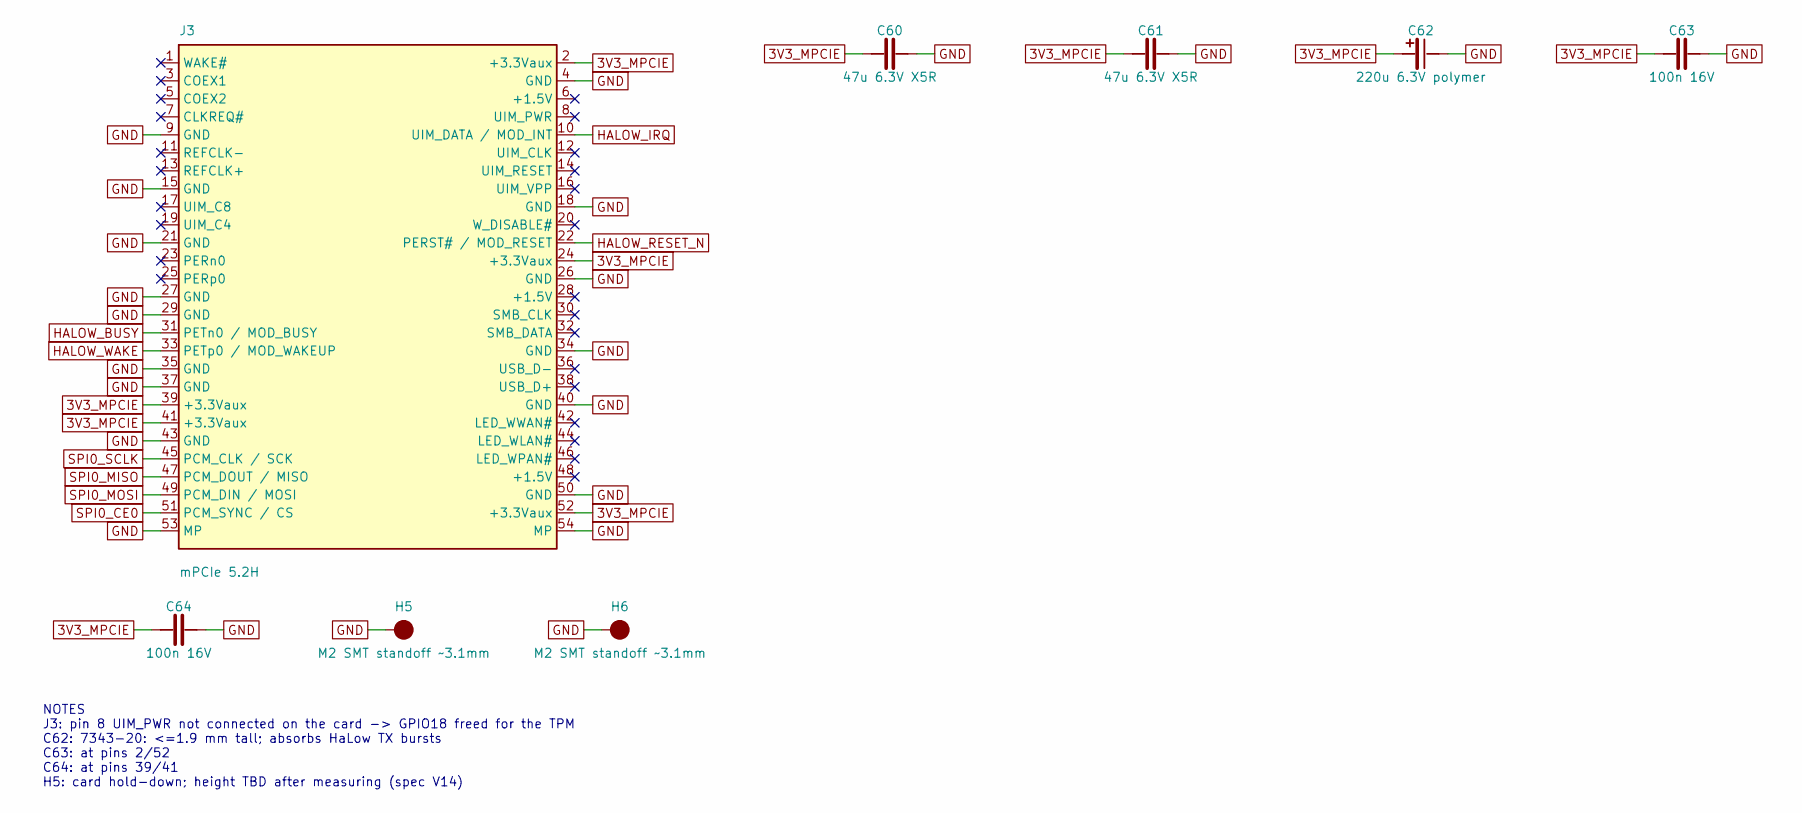
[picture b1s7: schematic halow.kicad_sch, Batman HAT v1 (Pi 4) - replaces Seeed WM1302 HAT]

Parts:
C60, C61: 47u 6.3V X5R; C_1206_3216Metric
C62: 220u 6.3V polymer; CP_EIA-7343-20_Kemet-V; MPN T520V227M006ATE015
C63, C64: 100n 16V; C_0402_1005Metric
H5, H6: M2 SMT standoff ~3.1mm; SMT_Standoff_M2_TBD
J3: mPCIe 5.2H; MiniPCIe_Lianxin_XDMP-052-A01_H5.2; MPN XDMP-052-A01; LCSC C7498130

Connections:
3V3_MPCIE: C60.1, C61.1, C62.1, C63.1, C64.1, J3.2 (+3.3Vaux), J3.24 (+3.3Vaux), J3.39 (+3.3Vaux), J3.41 (+3.3Vaux), J3.52 (+3.3Vaux); also elsewhere on the board
GND: C60.2, C61.2, C62.2, C63.2, C64.2, H5.1, H6.1, J3.4 (GND), J3.9 (GND), J3.15 (GND), J3.18 (GND), J3.21 (GND), J3.26 (GND), J3.27 (GND), J3.29 (GND), J3.34 (GND), J3.35 (GND), J3.37 (GND), J3.40 (GND), J3.43 (GND), J3.50 (GND), J3.53 (MP), J3.54 (MP); also elsewhere on the board
HALOW_BUSY: J3.31 (PETn0 / MOD_BUSY); also elsewhere on the board
HALOW_IRQ: J3.10 (UIM_DATA / MOD_INT); also elsewhere on the board
HALOW_RESET_N: J3.22 (PERST# / MOD_RESET); also elsewhere on the board
HALOW_WAKE: J3.33 (PETp0 / MOD_WAKEUP); also elsewhere on the board
SPI0_CE0: J3.51 (PCM_SYNC / CS); also elsewhere on the board
SPI0_MISO: J3.47 (PCM_DOUT / MISO); also elsewhere on the board
SPI0_MOSI: J3.49 (PCM_DIN / MOSI); also elsewhere on the board
SPI0_SCLK: J3.45 (PCM_CLK / SCK); also elsewhere on the board

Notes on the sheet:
NOTES J3: pin 8 UIM_PWR not connected on the card -> GPIO18 freed for the TPM C62: 7343-20: <=1.9 mm tall; absorbs HaLow TX bursts C63: at pins 2/52 C64: at pins 39/41 H5: card hold-down; height TBD after measuring (spec V14)

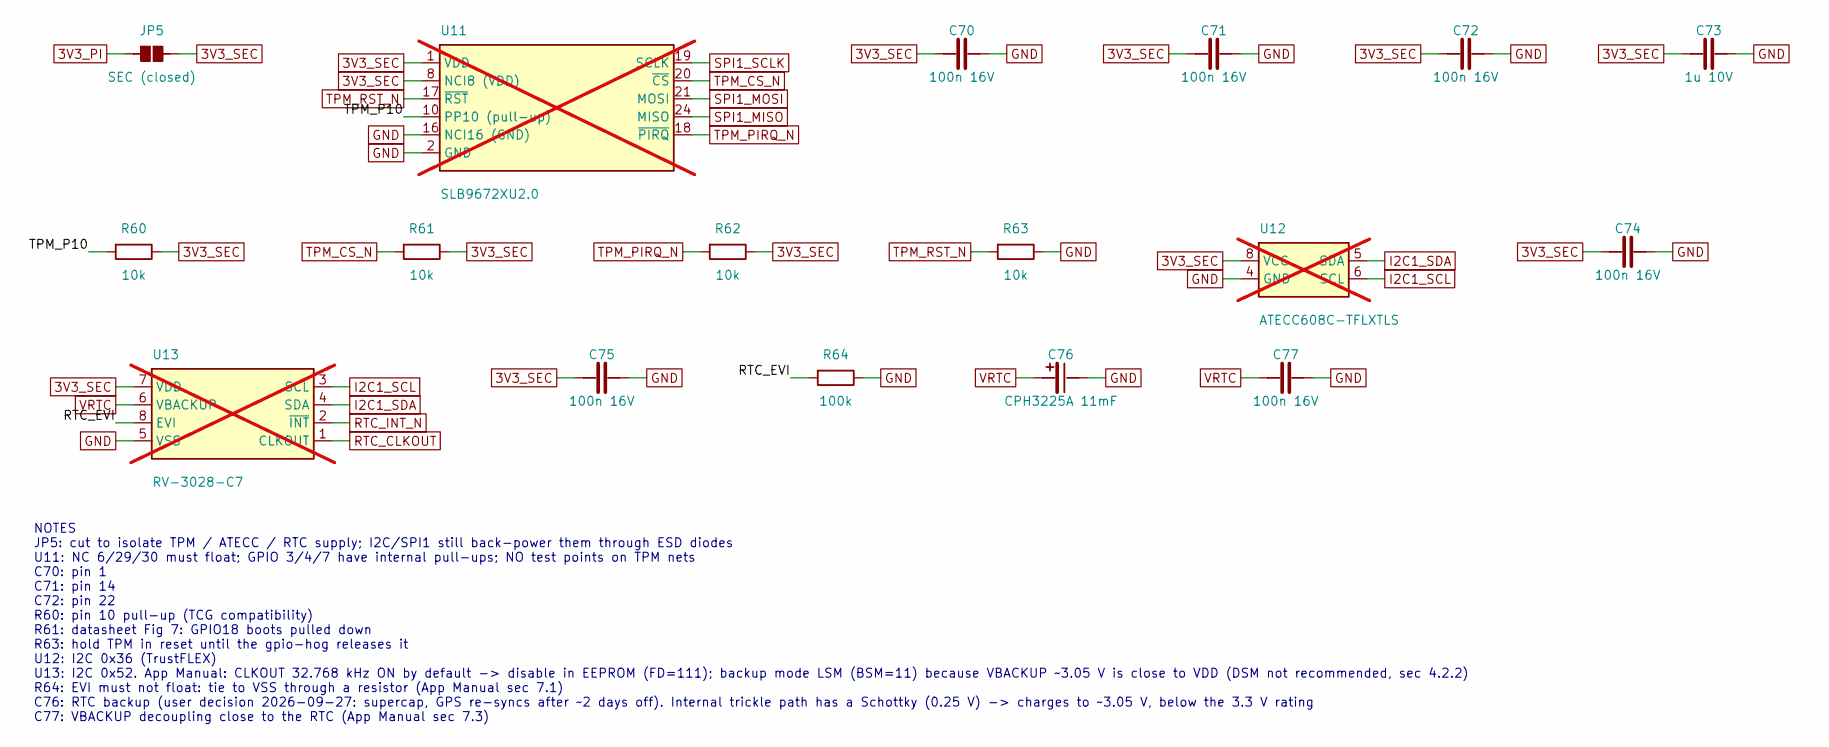
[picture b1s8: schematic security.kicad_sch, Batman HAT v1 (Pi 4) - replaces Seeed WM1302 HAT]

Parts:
C70, C71, C72, C74, C75, C77: 100n 16V; C_0402_1005Metric
C73: 1u 10V; C_0402_1005Metric
C76: CPH3225A 11mF; Seiko_CPH3225A; MPN CPH3225A
JP5: SEC (closed); SolderJumper-2_P1.3mm_Bridged_RoundedPad1.0x1.5mm
R60, R61, R62, R63: 10k; R_0402_1005Metric
R64: 100k; R_0402_1005Metric
U11: SLB9672XU2.0; QFN-32-1EP_5x5mm_P0.5mm_EP3.6x3.6mm; MPN SLB9672XU2.0 (orderable code: verify at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; not fitted
U12: ATECC608C-TFLXTLS; SOIC-8_3.9x4.9mm_P1.27mm; MPN ATECC608C-TFLXTLS (SOIC-8 suffix: verif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; not fitted
U13: RV-3028-C7; MicroCrystal_RV-3028-C7; MPN RV-3028-C7 32.768kHz 1ppm TA QC; not fitted

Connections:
3V3_SEC: C70.1, C71.1, C72.1, C73.1, C74.1, C75.1, JP5.2, R60.2, R61.2, R62.2, U11.1 (VDD), U11.8 (NCI8 (VDD)), U11.14 (VDD), U11.22 (VDD), U12.8 (VCC), U13.7 (VDD); also elsewhere on the board
GND: C70.2, C71.2, C72.2, C73.2, C74.2, C75.2, C76.2, C77.2, R63.2, R64.2, U11.2 (GND), U11.9 (GND), U11.16 (NCI16 (GND)), U11.23 (GND), U11.32 (GND), U11.33 (GND), U12.4 (GND), U13.5 (VSS); also elsewhere on the board
I2C1_SCL: U12.6 (SCL), U13.3 (SCL); also elsewhere on the board
I2C1_SDA: U12.5 (SDA), U13.4 (SDA); also elsewhere on the board
RTC_CLKOUT: U13.1 (CLKOUT); also elsewhere on the board
RTC_EVI: R64.1, U13.8 (EVI)
RTC_INT_N: U13.2 (~INT); also elsewhere on the board
SPI1_MISO: U11.24 (MISO); also elsewhere on the board
SPI1_MOSI: U11.21 (MOSI); also elsewhere on the board
SPI1_SCLK: U11.19 (SCLK); also elsewhere on the board
TPM_CS_N: R61.1, U11.20 (~CS); also elsewhere on the board
TPM_P10: R60.1, U11.10 (PP10 (pull-up))
TPM_PIRQ_N: R62.1, U11.18 (~PIRQ); also elsewhere on the board
TPM_RST_N: R63.1, U11.17 (~RST); also elsewhere on the board
VRTC: C76.1, C77.1, U13.6 (VBACKUP); also elsewhere on the board

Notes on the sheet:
NOTES JP5: cut to isolate TPM / ATECC / RTC supply; I2C/SPI1 still back-power them through ESD diodes U11: NC 6/29/30 must float; GPIO 3/4/7 have internal pull-ups; NO test points on TPM nets C70: pin 1 C71: pin 14 C72: pin 22 R60: pin 10 pull-up (TCG compatibility) R61: datasheet Fig 7: GPIO18 boo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
